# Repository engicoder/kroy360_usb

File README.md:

Kroy 360 USB converter with display
======================

This converter interfaces the display and keyboard directly, bypassing the 
original main board. The controller receives key events from the keyboard 
and maps them into USB key codes which are then sent via the USB connection to 
the host. The key events are simultaneously translated into ascii characters 
to be output on the lcd display. Text from the keyboard is displayed as a single 
line which is cleared when pressing enter or escape. The key stroke count of the
current line is also displayed.

## Interfacing

The converter PCB connects to the display using the 10 pin header marked 
"DISPLAY" and to the keyboard via a 20 pin ribbon cable connected to the header
marked "KEYBOARD". The other end of the ribbon cable connects to the 20 pin 
header on the keyboard assembly. 

###  Pinouts

#### Keyboard
<table>
    <tr><td>1</td><td>P1 (pulse 1)</td><td>2</td><td>P2 (pulse 2)</td></tr>
    <tr><td>3</td><td>KS (key state)</td><td>4</td><td>EM_LED</td></tr>
    <tr><td>5</td><td>D6 (data 6)</td><td>6</td><td>TS_LED</td></tr>
    <tr><td>7</td><td>D5 (data 5)</td><td>8</td><td>CL_LED</td></tr>
    <tr><td>9</td><td>D4 (data 4)</td><td>10</td><td>GND</td></tr>
    <tr><td>11</td><td>D3 (data 3))</td><td>12</td><td>GND</td></tr>
    <tr><td>13</td><td>D2 (data 2)</td><td>14</td><td>GND</td></tr>
    <tr><td>15</td><td>D1 (data 1)</td><td>16</td><td>GND</td></tr>
    <tr><td>17</td><td>D0 (data 0)</td><td>18</td><td>GND</td></tr>
    <tr><td>19</td><td>VCC (KB pwr)</td><td>20</td><td>EX</td></tr>
</table>   

#### Display
<table>
    <tr><td>1</td><td>FLM</td></tr>
    <tr><td>2</td><td>M</td></tr>
    <tr><td>3</td><td>CL1</td></tr>
    <tr><td>4</td><td>D</td></tr>
    <tr><td>5</td><td>CL2</td></tr>
    <tr><td>6</td><td>VDD (+5V)</td></tr>
    <tr><td>7</td><td>VSS</td></tr>
    <tr><td>8</td><td>VEE (-5V)</td></tr>
    <tr><td>9</td><td>VO (bias)</td></tr>
    <tr><td>10</td><td>NC</td></tr>
</table>   

### Operation

#### Data
Data is received from the keyboard as a 7 bit scan code on data lines *D0..D6*. 
Each key position has a unique scan code. The up or down state of the key is set
by the *KS* line with a high value indicating the down state and a low value 
indicating the up state.  The *P1* line is pulled low by the keyboard when a key
state change has been detected. The converter reads the data including key state
and then pulls *P2* low momentary (~20us) to release the keyboards data latch.
If multiple keys are down, the *KS* line indicates the state of the last key change.

#### Status LEDs
The keyboard has 3 keys with integrated status LEDs; *Caps Lock*, *Type Specs* and
*Edit Mode*. Each LED has a dedicated interface line. Pulling the line low turns 
the LED on.

#### Display
The display is a Hitachi H2525 239x20 dot graphical lcd display. The display 
does not have a dedicated controller. The rows and columns of the display are 
driven by a chain of HD44104 shift registers. Data must be sent as a continuous,
synchronous data stream using data line *D* and clock line *CL2*. The *CL1* line 
latches each 239 bit row of data. The *FLM* line indicates the beginning of a new 
frame of data. Each frame is 20 rows of data. The *M* line is the polarity of the 
LCD drive voltage. The *M* line should be toggled every frame or the intensity of 
the pixels will fade. The display requires both a +5V (*VDD*) and -5V (*VEE*) 
supply. The *VO* line a bias voltage that changes the angle from which the pixels 
can be seen.

## Hardware

The custom PCB uses an ATmega32U4 microcontroller to read data from the keyboard,
drive the display, and send received key events over USB to the host by means of
a custom firmware driver. The +5V and -5V supplies for the display are generated
from the 5V provided by USB using the TC1044S charge pump. The display bias 
voltage VO is created using a potentiometer. The outer pins of the potentiometer
are attached to +5V and -5V; the center tap connected to VO. A TPS22929D load 
switch allows the firmware to control when USB 5V power is connected to the 
keyboard VCC pin. An on board LED is used for firmware status. It will flash 
during start up and once when a key event is received. 

## Firmware

The firmware is written to use the QMK keyboard firmware framework. 
https://github.com/qmk/qmk_firmware
### Build
To build the firmware:

* Clone the QMK repository and sub modules into a local folder
* Create a new folder, 'kroy360_usb', under 'qmk_firmware/keybords/converter'
* Copy the contents of the 'firmware' directory in this repository to the new 
'kroy360_usb' folder

From the qmk_firmware root:

    $ make converter/kroy360_usb:default

### Features

#### Password blanking
A custom QMK keycode, **PWD_TOG**, has been defined that can be assigned to any key.
When pressed, this keycode will toggle the password blanking feature. When active 
password blanking replaces the ascii characters for a given keystroke with an 
asterisk '*'. In the default keymap, **PWD_TOG** is assigned to the *Type Specs* 
key and the integrated LED will turn on when password blanking is active.

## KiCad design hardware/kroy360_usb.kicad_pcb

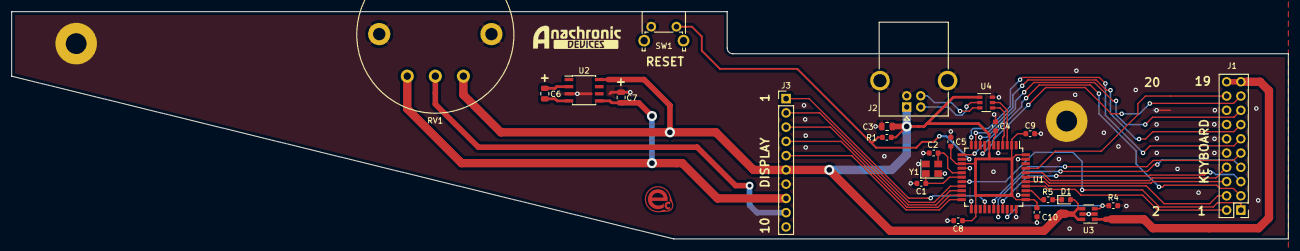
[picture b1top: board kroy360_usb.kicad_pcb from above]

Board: 2 copper layers, 227.5 x 40.5 mm, 26 parts (0 on the bottom side), 37 nets.

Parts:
C1, C2: 22pF; C_0603_1608Metric
C3: 4.7uF; C_0805_2012Metric
C4: 1uF; C_0603_1608Metric
C5, C8, C9, C10: 0.1uF; C_0603_1608Metric
C6, C7: 10uF; C_0805_2012Metric
D1: LED_ALT; LED_0603_1608Metric
J1: Keyboard; PinHeader_2x10_P2.54mm_Vertical
J2: USB_B; USB_B_OST_USB-B1HSxx_Horizontal
J3: Display; PinHeader_1x10_P2.54mm_Vertical
MH1, MH2: MountingHole_Pad-Mechanical; MountingHole_3.7mm_Pad
R1, R4: 10K; R_0603_1608Metric
R5: 1K; R_0603_1608Metric
RV1: LCD Contrast; Potentiometer-Piher-T-18A
SW1: SW_Push; SW_Tactile_SPST_Angled_PTS645Vx83-2LFS
U1: ATmega32U4-AU; TQFP-44_10x10mm_P0.8mm
U2: TC1044S; SOIC-8_3.9x4.9mm_P1.27mm
U3: TPS22929D; SOT-23-6
U4: STF202; TSOP-6_1.5x3mm_P0.95mm
Y1: 16MHz/16pF; Crystal_SMD_3225-4Pin_3.2x2.5mm

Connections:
+5V: C3.1, C5.1, C8.1, C9.1, C10.1, D1.2, J2.1, J3.6, R1.1, RV1.1, U1.2, U1.7, U1.14, U1.24, U1.34, U1.44, U2.8, U3.4, U3.6, U4.1
-5V: C7.2, J3.8, RV1.3, U2.5
/CL1: J3.3, U1.20
/CL2: J3.5, U1.22
/CL_LED: J1.8, U1.40
/D: J3.4, U1.21
/D0: J1.17, U1.8
/D1: J1.15, U1.9
/D2: J1.13, U1.10
/D3: J1.11, U1.11
/D4: J1.9, U1.28
/D5: J1.7, U1.29
/D6: J1.5, U1.30
/EM_LED: J1.4, U1.38
/EX: J1.18, U1.41
/FLM: J3.1, U1.26
/KB_EN: R4.1, U1.31, U3.3
/KS: J1.3, U1.12
/LED: R5.2, U1.36
/M: J3.2, U1.19
/P1: J1.1, U1.18
/P2: J1.2, U1.37
/RESET: R1.2, SW1.2, U1.13
/TS_LED: J1.6, U1.39
/USB_DM: J2.2, U4.2
/USB_DP: J2.3, U4.3
/VKB: J1.19, J1.20, U3.1
/VO: J3.9, RV1.2
/XTAL1: C1.1, U1.17, Y1.1
/XTAL2: C2.1, U1.16, Y1.3
GND: C1.2, C2.2, C3.2, C4.2, C5.2, C7.1, C8.2, C9.2, C10.2, J1.10, J1.12, J1.14, J1.16, J2.4, J2.5, J3.7, MH1.1, MH2.1, R4.2, RV1.MP, SW1.1, U1.5, U1.15, U1.23, U1.33, U1.35, U1.43, U2.3, U3.2, U3.5, U4.6, Y1.2, Y1.4
unnamed: C4.1, U1.6
unnamed: C6.1, U2.2
unnamed: C6.2, U2.4
unnamed: D1.1, R5.1
unnamed: U1.3, U4.5
unnamed: U1.4, U4.4

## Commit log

2020-07-01 Initial version
2020-07-01 Fixed formatting and typos
2021-02-07 Updates for rev B
2021-02-07 Rename kroy360 to kroy360_usb
2021-02-07 Rename kroy360 to kroy360_usb 0d8c698
